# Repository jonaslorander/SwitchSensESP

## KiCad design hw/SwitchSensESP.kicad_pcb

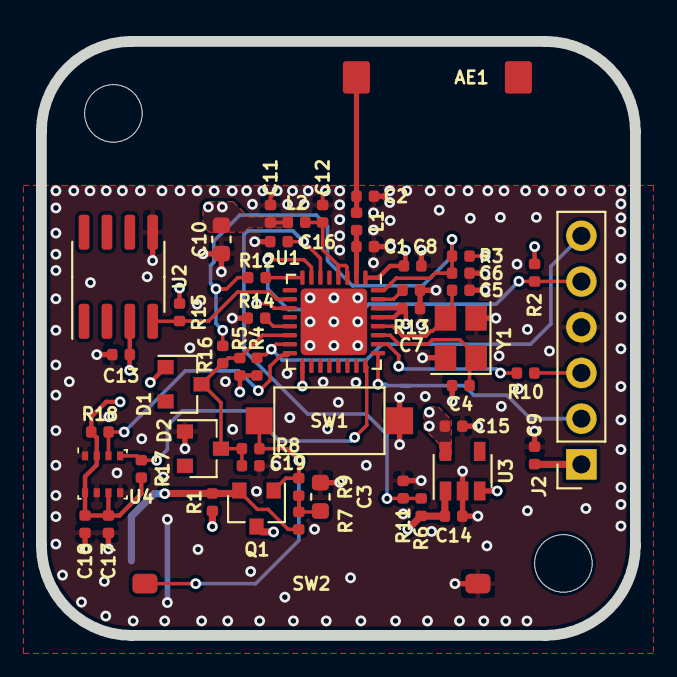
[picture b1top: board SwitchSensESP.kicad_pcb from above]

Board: 4 copper layers, 33.0 x 33.0 mm, 54 parts (1 on the bottom side), 25 nets.

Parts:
AE1: Antenna_Chip; JOHANSON_2450AT45A100
C1: 4.7p; C_0402_1005Metric
C2: 3.9p; C_0402_1005Metric
C3, C10: 10u; C_0603_1608Metric
C4, C5: 10p; C_0402_1005Metric
C6, C8, C9, C11, C12, C13, C16, C17, C18: 100n; C_0402_1005Metric
C7, C14, C15: 1u; C_0402_1005Metric
C19: 10n; C_0402_1005Metric
D1: BAT54A; SOT-23
D2: BZX84C3V6; D_SOT-23_ANK
H1, H2: 3.2 mm; MountingHole_3.2mm_M3
J1: Conn_01x02; JST_PH_S2B-PH-SM4-TB_1x02-1MP_P2.00mm_Horizontal
J2: Conn_01x06; PinSocket_1x06_P2.54mm_Vertical
L1: 1.8n; L_0402_1005Metric
L2: 0R; L_0402_1005Metric
Q1: SSM3J328R; SOT-23
R1: 0R; R_0402_1005Metric
R2, R3, R4, R5, R14: 10k; R_0402_1005Metric
R6, R7: 100k; R_0402_1005Metric
R8, R9, R12, R16: 220R; R_0402_1005Metric
R10: 499R; R_0402_1005Metric
R11: 33k; R_0402_1005Metric
R13: 12k; R_0402_1005Metric
R15, R17, R18: 4k7; R_0402_1005Metric
SW1: RS282G05A3SMRT; SW_SPST_CK_RS282G05A3
SW2: MK15-B-2-OE; STANDEX_MK15
U1: ESP8285; QFN-32-1EP_5x5mm_P0.5mm_EP3.7x3.7mm
U2: DS18B20Z; SOIC-8_3.9x4.9mm_P1.27mm
U3: AP2112K-3.3; SOT-23-5
U4: BME280; Bosch_LGA-8_2.5x2.5mm_P0.65mm_ClockwisePinNumbering
Y1: 26MHz; Crystal_SMD_3225-4Pin_3.2x2.5mm

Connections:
+VDC: C9.1, C14.1, J2.1, Q1.3, R1.1, R6.1, U3.1, U3.3
/ADC: C16.1, R6.2, R11.1, U1.6
/CHIP_EN: J2.5, R2.2, U1.7
/GPIO0: J2.6, R4.2, U1.15
/I2C_SCL: R17.2, U1.24, U4.4
/I2C_SDA: R18.2, U1.16, U4.3
/ONEWIRE: R15.2, U1.10, U2.4
/RXD: J2.2, U1.25
/TXD: J2.3, R10.1
/WAKE: R12.2, U1.8
/~ON: C19.1, D1.3, D2.1, R5.2, R8.1, R16.2, U1.14
/~RESET: C6.1, R3.2, R12.1, R16.1, U1.32
GND: C1.2, C2.2, C3.2, C4.2, C5.2, C6.2, C7.2, C8.2, C9.2, C10.2, C11.2, C12.2, C13.2, C14.2, C15.2, C16.2, C17.2, C18.2, C19.2, D2.2, J1.2, J2.4, R11.2, R13.2, R14.2, SW1.1, SW2.2, U1.33, U2.5, U3.2, U4.1, U4.5, U4.7, Y1.2, Y1.4
unnamed: AE1.1, C2.1, L1.2
unnamed: C1.1, L1.1, U1.2
unnamed: C3.1, R7.2, R9.2
unnamed: C4.1, U1.27, Y1.1
unnamed: C5.1, U1.28, Y1.3
unnamed: C12.1, L2.2, U1.3, U1.4
unnamed: J1.1, Q1.2, R1.2, R7.1
unnamed: Q1.1, R8.2, R9.1, SW1.2, SW2.1
unnamed: R10.2, U1.26
unnamed: R13.1, U1.31
unnamed: R14.1, U1.13
VDD: C7.1, C8.1, C10.1, C11.1, C13.1, C15.1, C17.1, C18.1, D1.1, L2.1, R2.1, R3.1, R4.1, R5.1, R15.1, R17.1, R18.1, U1.1, U1.11, U1.17, U1.29, U1.30, U2.3, U3.5, U4.2, U4.6, U4.8

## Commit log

2020-06-14 v2020-04-22
